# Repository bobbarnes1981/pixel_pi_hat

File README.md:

# pixel_pi_hat

https://github.com/raspberrypi/hats/blob/master/uhat-board-mechanical.pdf

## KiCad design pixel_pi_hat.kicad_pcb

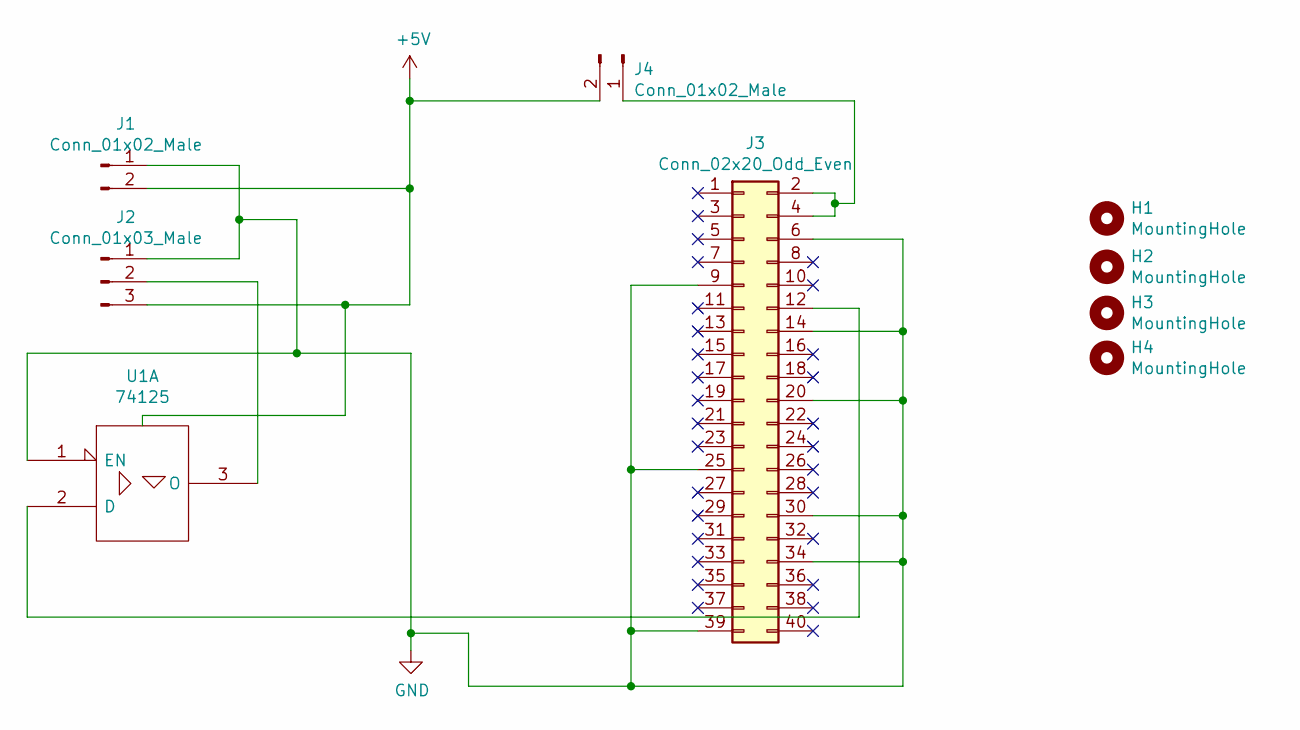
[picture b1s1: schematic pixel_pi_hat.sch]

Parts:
H1, H2, H3, H4: MountingHole; MountingHole_2.7mm_M2.5_Pad
J1: Conn_01x02_Male; TerminalBlock_WAGO_804-102_1x02_P5.00mm_45Degree
J2: Conn_01x03_Male; TerminalBlock_WAGO_804-103_1x03_P5.00mm_45Degree
J3: Conn_02x20_Odd_Even; PinHeader_2x20_P2.54mm_Vertical
J4: Conn_01x02_Male; PinHeader_1x02_P2.54mm_Vertical
U1: 74125; DIP-14_W7.62mm_LongPads

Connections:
+5V: J1.2, J2.3, J4.2, U1.14 (VCC)
GND: J1.1, J2.1, J3.6, J3.9, J3.14, J3.20, J3.25, J3.30, J3.34, J3.39, U1.1 (EN), U1.7 (GND)
unnamed: J2.2, U1.3 (O)
unnamed: J3.2, J3.4, J4.1
unnamed: J3.12, U1.2 (D)

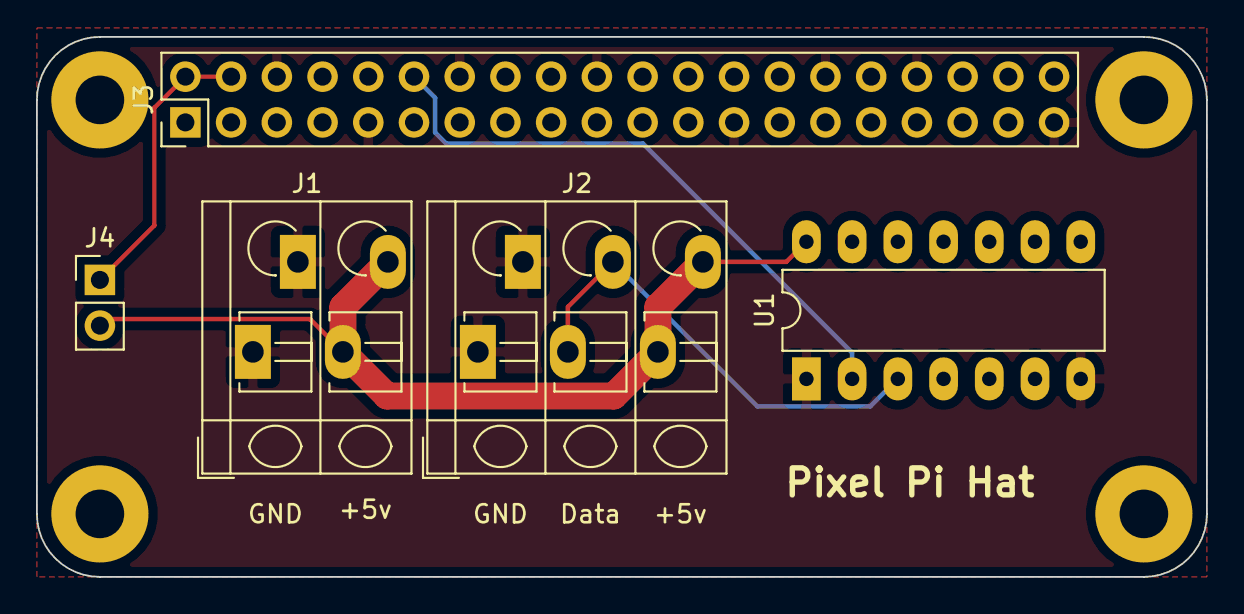
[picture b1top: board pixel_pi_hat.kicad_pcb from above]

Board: 2 copper layers, 65.0 x 30.0 mm, 9 parts (0 on the bottom side), 5 nets.

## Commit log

2021-09-28 Add kicad files
2021-09-28 Add gerber files
2021-10-07 Change to wago 804 push button terminals
